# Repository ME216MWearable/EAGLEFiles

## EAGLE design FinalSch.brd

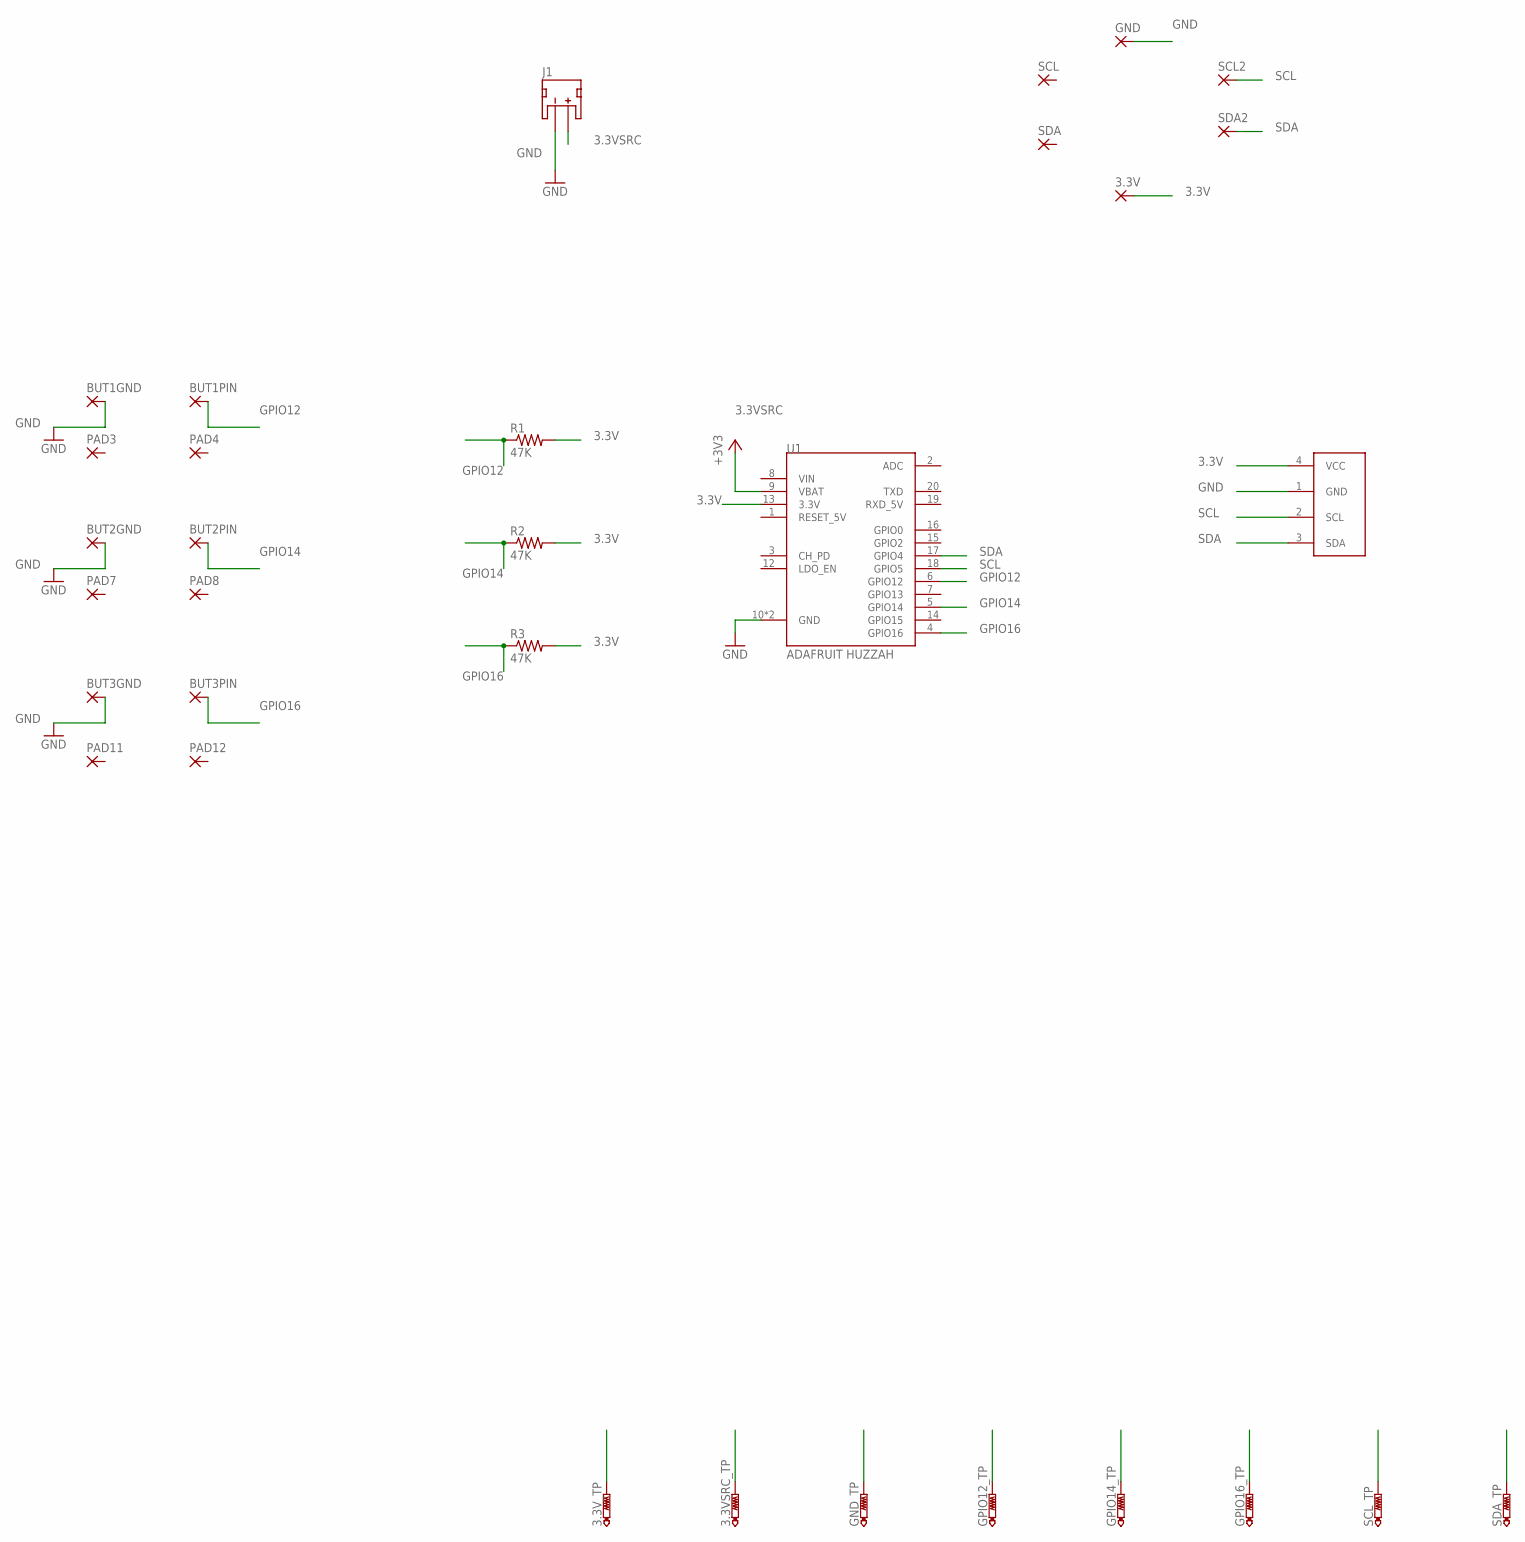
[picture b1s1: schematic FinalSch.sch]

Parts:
3.3V: 2,54/1,1
3.3VSRC_TP, 3.3V_TP: PTR1B1,27; B1,27
BUT1GND, BUT1PIN, BUT2GND, BUT2PIN, BUT3GND, BUT3PIN: SMD2; SMD1,27-2,54
GND: 2,54/1,1
GND_TP: PTR1B1,27; B1,27
GPIO12_TP, GPIO14_TP, GPIO16_TP: PTR1B1,27; B1,27
J1: JST_2MM_MALE; JST-2-SMD
PAD3, PAD4, PAD7, PAD8, PAD11, PAD12: SMD2; SMD1,27-2,54
R1, R2, R3: 47K; R0805
SCL, SCL2: 2,54/1,1
SCL_TP: PTR1B1,27; B1,27
SDA, SDA2: 2,54/1,1
SDA_TP: PTR1B1,27; B1,27
U1: ADAFRUIT_HEZZAH; ADAFRUIT_HUZZAH
U$1: I2C_OLED; I2C_OLED_PACKAGE

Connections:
3.3V: 3.3V.1, 3.3V_TP.TP, R1.2, R2.2, R3.2, U1.13 (3.3V), U$1.4 (VCC)
3.3VSRC: 3.3VSRC_TP.TP, J1.2 (+), U1.9 (VBAT)
GND: BUT1GND.1, BUT2GND.1, BUT3GND.1, GND.1, GND_TP.TP, J1.1 (-), U1.10 (GND), U1.11 (GND), U$1.1 (GND)
GPIO12: BUT1PIN.1, GPIO12_TP.TP, R1.1, U1.6 (GPIO12)
GPIO14: BUT2PIN.1, GPIO14_TP.TP, R2.1, U1.5 (GPIO14)
GPIO16: BUT3PIN.1, GPIO16_TP.TP, R3.1, U1.4 (GPIO16)
SCL: SCL2.1, SCL_TP.TP, U1.18 (GPIO5), U$1.2 (SCL)
SDA: SDA2.1, SDA_TP.TP, U1.17 (GPIO4), U$1.3 (SDA)

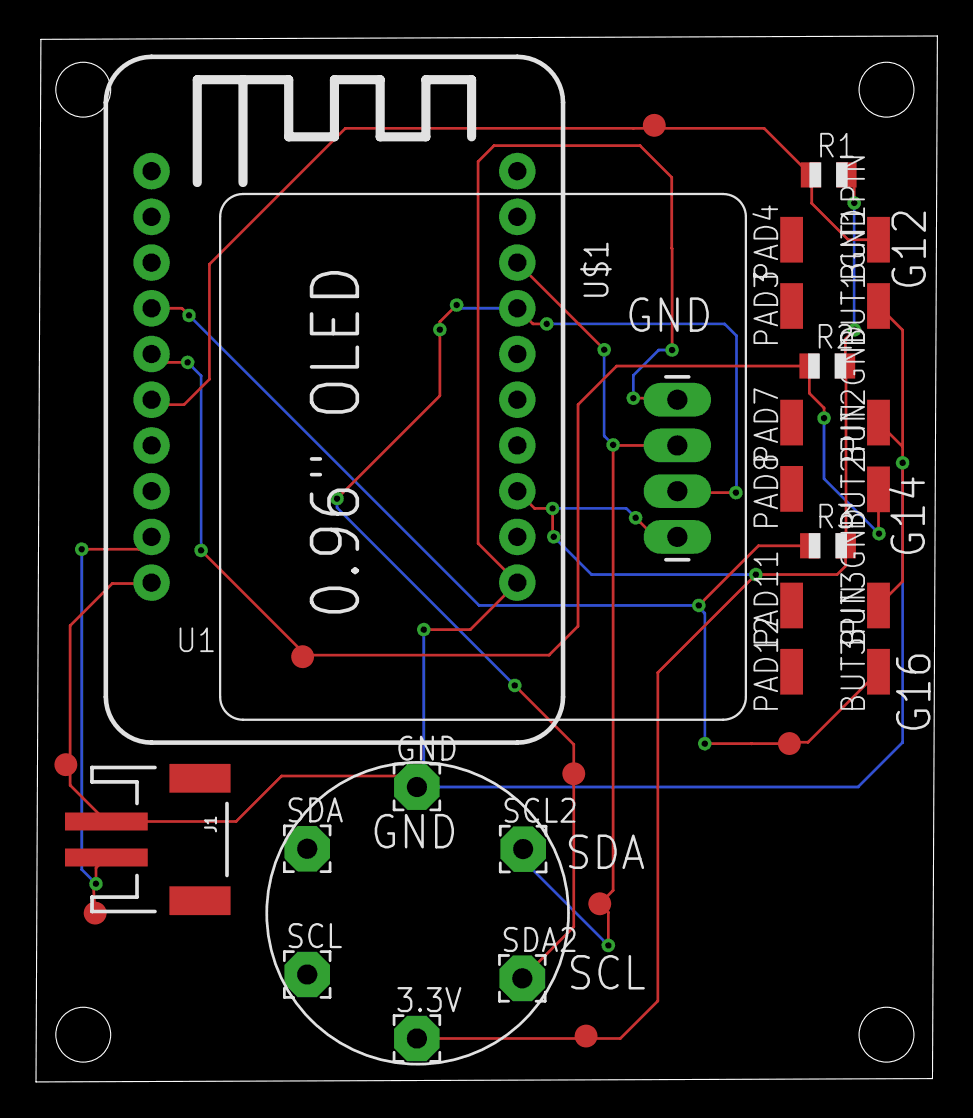
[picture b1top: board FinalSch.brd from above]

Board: 2 copper layers, 50.1 x 58.1 mm, 32 parts (0 on the bottom side), 8 nets.

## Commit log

2018-06-11 EAGLE Files

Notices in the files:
parts and their libraries:
SparkFun-Connectors: Licensing: Creative Commons ShareAlike 4.0 International - https://creativecommons.org/licenses/by-sa/4.0
